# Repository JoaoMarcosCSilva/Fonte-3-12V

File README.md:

# Fonte 3-12V
 Circuito de uma fonte de 100mA de 3 a 12 volts
 Para executar o código com os cálculos dos valores finais obtidos (listados abaixo), execute:
 
    python script.py

[Circuito Ideal](http://tinyurl.com/yblvf7et)

[Circuito Real](http://tinyurl.com/ybcebmec)

[Vídeo](https://youtu.be/PqBpsNU2R8g)

## Circuito

## Esquemático

## PCB

Valores pré-determinados:
- Tensão máxima e mínima: 12v e 3v
- Queda de tensão entre a base do primeiro transistor e o emissor do último: 1.292V (medido no falstad, muda levemente para correntes diferentes)
- Resistência do resistor à direita do potenciômetro: 4k3 (explicação abaixo)
- Ganho dos transistores: 200 (explicação abaixo)
- Corrente máxima na base do transistor: 2.475 uA (medido no falstad)
- Tensão mínima garantida pelo capacitor: 19v (o mesmo teve sua capacitância escolhida de modo a garantir esse valor)
- Tensão de quebra do diodo zener: 15v (explicação abaixo)

Valores calculados a partir dos definidos acima:
- Resistência máxima do potenciômetro: calculada em 8997.001013056068
- Resistência do resistor à esquerda do potenciômetro (entre o mesmo e o diodo zener): calculada em 1704.4225888350963
- Resistência acima do diodo zener: calculada em 3991.6219879041864

# Preços dos Componentes
OBS: Preços atualizados em 20/06/2020
## Resistor à direita do potenciômetro
- 1 resistor 4k3 de 1/4 W (A potência real não passará de 4mW): R$0.08 ([loja](https://www.baudaeletronica.com.br/resistor-4k3-5-1-4w.html))
## Resistor à esquerda do potenciômetro
O valor calculado de 1704.4225888350963 será aproximado por um resistor de 1k5 (a diferença é usada pra garantir uma margem de erro)
- 1 resistor 1k5 de 1/4 W (A potência real não passará de 450uW): R$0.08 ([loja](https://www.baudaeletronica.com.br/resistor-1k5-5-1-4w.html))
## Potenciômetro
O valor calculado de  8997.001013056068 será aproximado por um potenciômetro de 10k (que não deve ser rotacionado até o gim)
- 1 Potenciômetro Linear de 10k com potência máxima de 0.2W: R$ 1,46  ([loja](https://www.baudaeletronica.com.br/potenciometro-linear-de-10k-10000.html))
## Resistor acima do diodo zener
O valor calculado de 3991.6219879041864 será aproximado por dois resistores de 2k em série
- 2 resistores 2k de 1/4 W (A potência real não passará de 20mW): R$0.08 cada ([loja](https://www.baudaeletronica.com.br/resistor-2k-5-1-4w.html))
## Capacitor
- 1 capacitor de 220uF e 35V (A tensão real não passará de 25V): R$ 0,38 (([loja](https://www.baudaeletronica.com.br/capacitor-eletrolitico-220uf-35v.html)))
## Diodo zener
- 1 diodo zener 1N5245 [15V / 0.5W] (A potência real não passará de 30mW): R$ 0,12  ([loja](https://www.baudaeletronica.com.br/diodo-zener-1n5245-15v-0-5w.html))
## Transformador
- 1 transformador de 127v para 18v, com corrente máxima 3A (A corrente real chegará próxima de 1.3A em cada ciclo ao carregar o capacitor, mas pode ultrapassar 2.6A no primeiro ciclo): R$ 49.99 ([loja](https://produto.mercadolivre.com.br/MLB-1300844398-transformador-1818v-3a-trafo-bivolt-_JM?quantity=1#position=1&type=item&tracking_id=ada41903-7303-418c-9af9-6d00176bfbd2))
## Ponte Retificadora
- 1 ponte retificadora KBU1010: R$3.70 ([loja](https://www.baudaeletronica.com.br/ponte-retificadora-kbu1010.html))
## Transistores
- 2 transistores NPN BC546 de ganho 200: R$0.24 cada ([loja](https://www.baudaeletronica.com.br/transistor-npn-bc546.html))

# O potenciômetro e resistores adjacentes
 No circuito, pode-se ver que existem dois resistores adjacentes ao potenciômetro.
 ## O resistor à direita
 O papel do resistor à direita do potenciômetro é limitar a corrente que passa pelo potenciômetro, reduzindo o gasto de energia.
 Porém, a sua resistência não pode ser muito alta, pois nesse caso a corrente que passa diretamente pelo potenciômetro seria muito pequena em relação à que passa pela base do transistor, o que faria a tensão final da fonte muito sensível a alterações na corrente.
 O seu valor (de 4k3) foi escolhido empiricamente após vários testes. Todos os outros componentes têm seus valores calculados a partir dessa escolha;

 ## O potenciômetro e o resistor à sua esquerda
 É garantido que a tensão em cima do diodo zener será sempre 13v. Assim, as resistências do resistor à esquerda do potenciômetro e do próprio potenciômetro podem ser calculadas para que a tensão de saída da fonte, a partir dos seguintes dados conhecidos:

- Resistência do resistor à direita do potenciômetro (definida em 4k3)
- Tensão do diodo zener (definida em 15v)
- Queda de tensão entre a base do primeiro transistor e o emissor do último (medida no falstad em 1.292V)
- Corrente máxima passando pela base do primeiro transistor (medido no falstad como 2.475uA)

# O diodo zener e o resistor acima dele
O diodo zener deve possuir uma tensão de quebra de 15v, para permitir produzir 12v na saída após a queda nos dois transistores
O valor do resistor acima dele foi calculado para que a tensão mínima em cima do zener seja sempre 15v, usando as seguintes informações:

- Tensão mínima garantida pelo capacitor (19v no caso)
- Tensão de quebra do diodo zener (15v)
- Corrente passando pelo próprio resistor (calculada com as resistências do potenciômetro e dos resistores adjacentes a ele, valores encontrados anteriormente, além da corrente na base do transistor)

Por não ser ideal, o diodo zener não "quebra" a tensão exatamente em 13v, mas um pouco abaixo, o que faz a tensão de saída oscilar um pouco

# O capacitor e o transformador
Foi escolhido um transformador de 127v para 18v e um capacitor de 220uF. Esses valores foram escolhidos para garantir uma tensão de no mínimo 19v no resistor acima do diodo zener, o qual teve seu valor calculado acima de modo a reduzir esse valor de 19v a um valor de no mínimo 15v (o excedente será absorvido pelo diodo zener).

# Os transistores e a corrente de saída
Utilizando os calculos acima, é possível criar um circuito que forneça exatamente as tensões desejadas para a corrente de 100mA pedida. Porém, erros começam a ocorrer quando uma corrente menor que 100mA é fornecida.

Para reduzir esse efeito, foram usados dois transistores de um ganho relativamente alto (200x), com o emissor do primeiro conectado na base do segundo. Isso tem o efeito de reduzir em muitas vezes a corrente que passa pela base do primeiro transistor (a qual é retirada do potenciômetro), tornando a tensão de saída mais robusta a variações de corrente

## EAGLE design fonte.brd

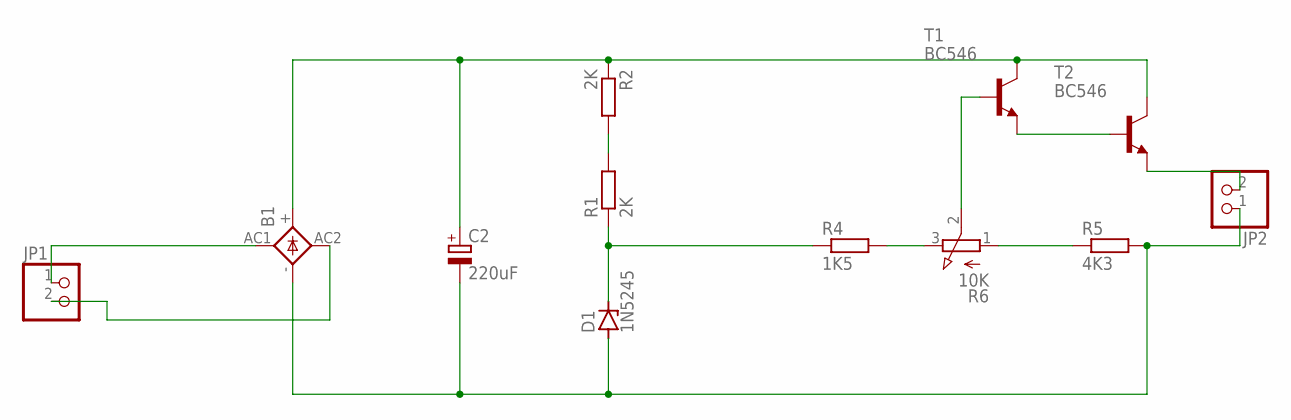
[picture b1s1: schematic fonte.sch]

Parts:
B1: KBU
C2: 220uF; E3,5-10
D1: 1N5245; DO41Z10
JP1, JP2: PINHD-1X2; 1X02
R1, R2: 2K; 0204/7
R4: 1K5; 0204/7
R5: 4K3; 0204/7
R6: 10K; 3RP/1610N
T1, T2: BC546; TO92

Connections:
unnamed: R1.2, R2.2
unnamed: D1.C, R1.1, R4.1
unnamed: T1.1 (E), T2.2 (B)
unnamed: R4.2, R6.3 (E)
unnamed: R5.1, R6.1 (A)
unnamed: R6.2 (S), T1.2 (B)
unnamed: B1.-, C2.-, D1.A, JP2.1, R5.2
unnamed: B1.+, C2.+, R2.1, T1.3 (C), T2.3 (C)
unnamed: JP2.2, T2.1 (E)
unnamed: B1.AC2, JP1.2
unnamed: B1.AC1, JP1.1

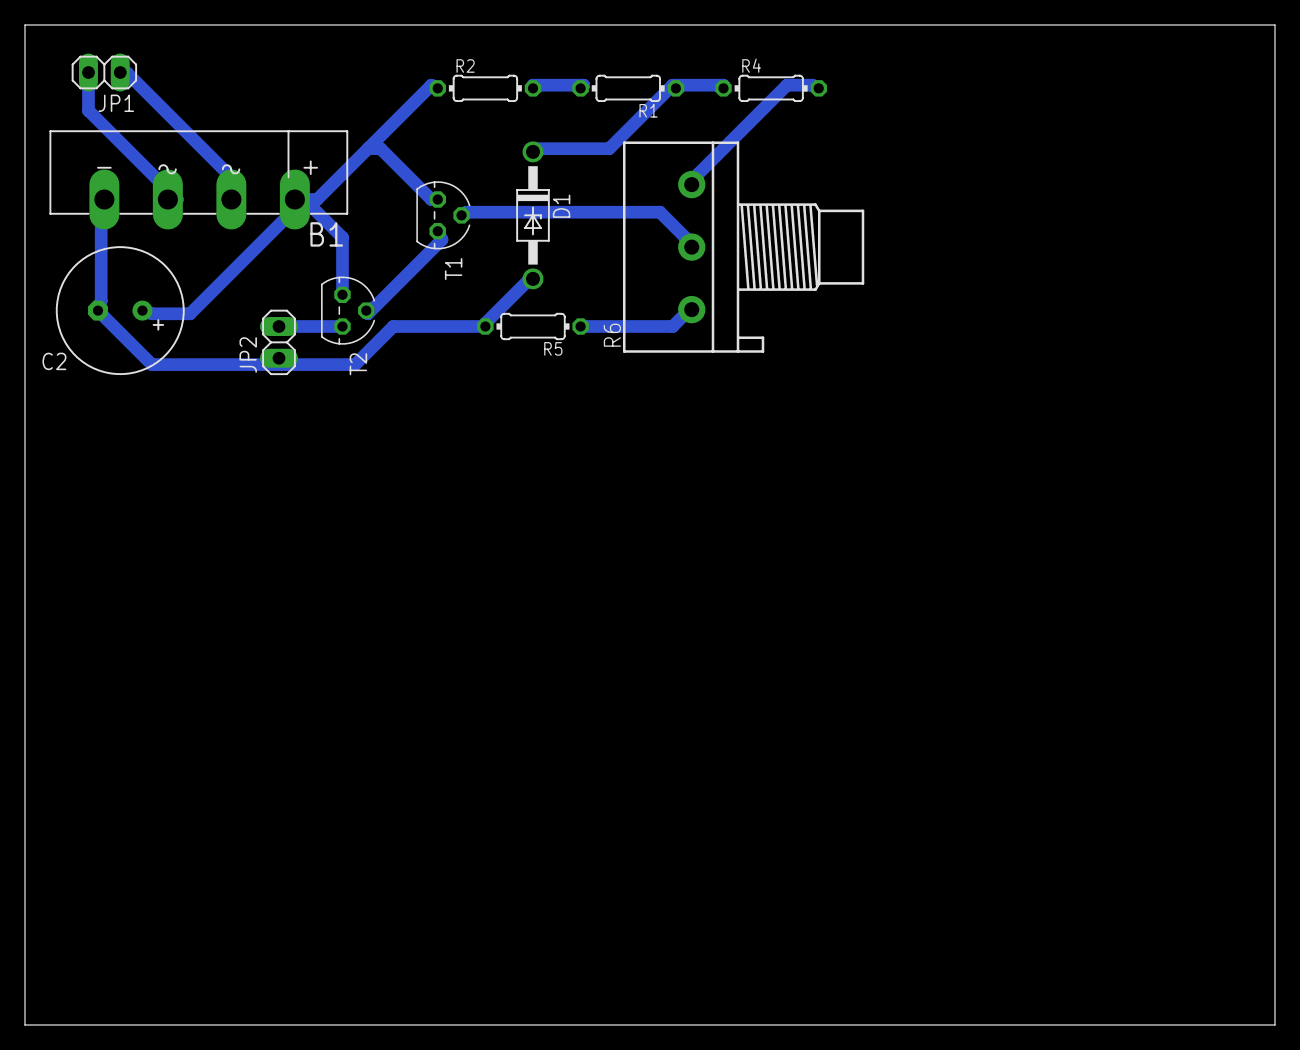
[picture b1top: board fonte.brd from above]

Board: 2 copper layers, 100.0 x 80.0 mm, 12 parts (0 on the bottom side), 11 nets.

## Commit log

2020-06-14 Create initial files
2020-06-14 Retira um argumento inutilizado da função get_max_Rz e adiciona uma documentação do README.md
2020-06-14 Corrige a formatação do README.md e retira código antigo, comentado, de script.py
2020-06-24 Adiciona os preços dos componentes
2020-06-24 Adiciona o preço do transformador
2020-06-24 Atualiza os valores do capacitor e transformador
2020-06-27 Adiciona a ponte retificadora
2020-06-29 Adiciona um circuito no falstad com os valores reais dos compontentes a serem comprados
2020-06-29 Corrige os valores para um transistor de ganho 200
2020-06-30 Muda os valores para o circuito de 2 transistores e atualiza as funções para o cálculo das resistências
2020-06-30 Atualiza o README com o circuito de 2 transistores
2020-06-30 Atualiza o README com a nova ponte retificadora
2020-07-01 Reescreve o código e atualiza o circuito ideal
2020-07-01 Adiciona links no README
2020-07-09 Adiciona imagens e arquivos do EAGLE Please enter the commit message for your changes. Lines starting
2020-07-09 Adiciona link para o vídeo
